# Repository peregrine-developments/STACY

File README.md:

# STACY
Requires symbols/footprints from [TheBoisCollective global library ](https://github.com/peregrine-developments/TBC_Global)

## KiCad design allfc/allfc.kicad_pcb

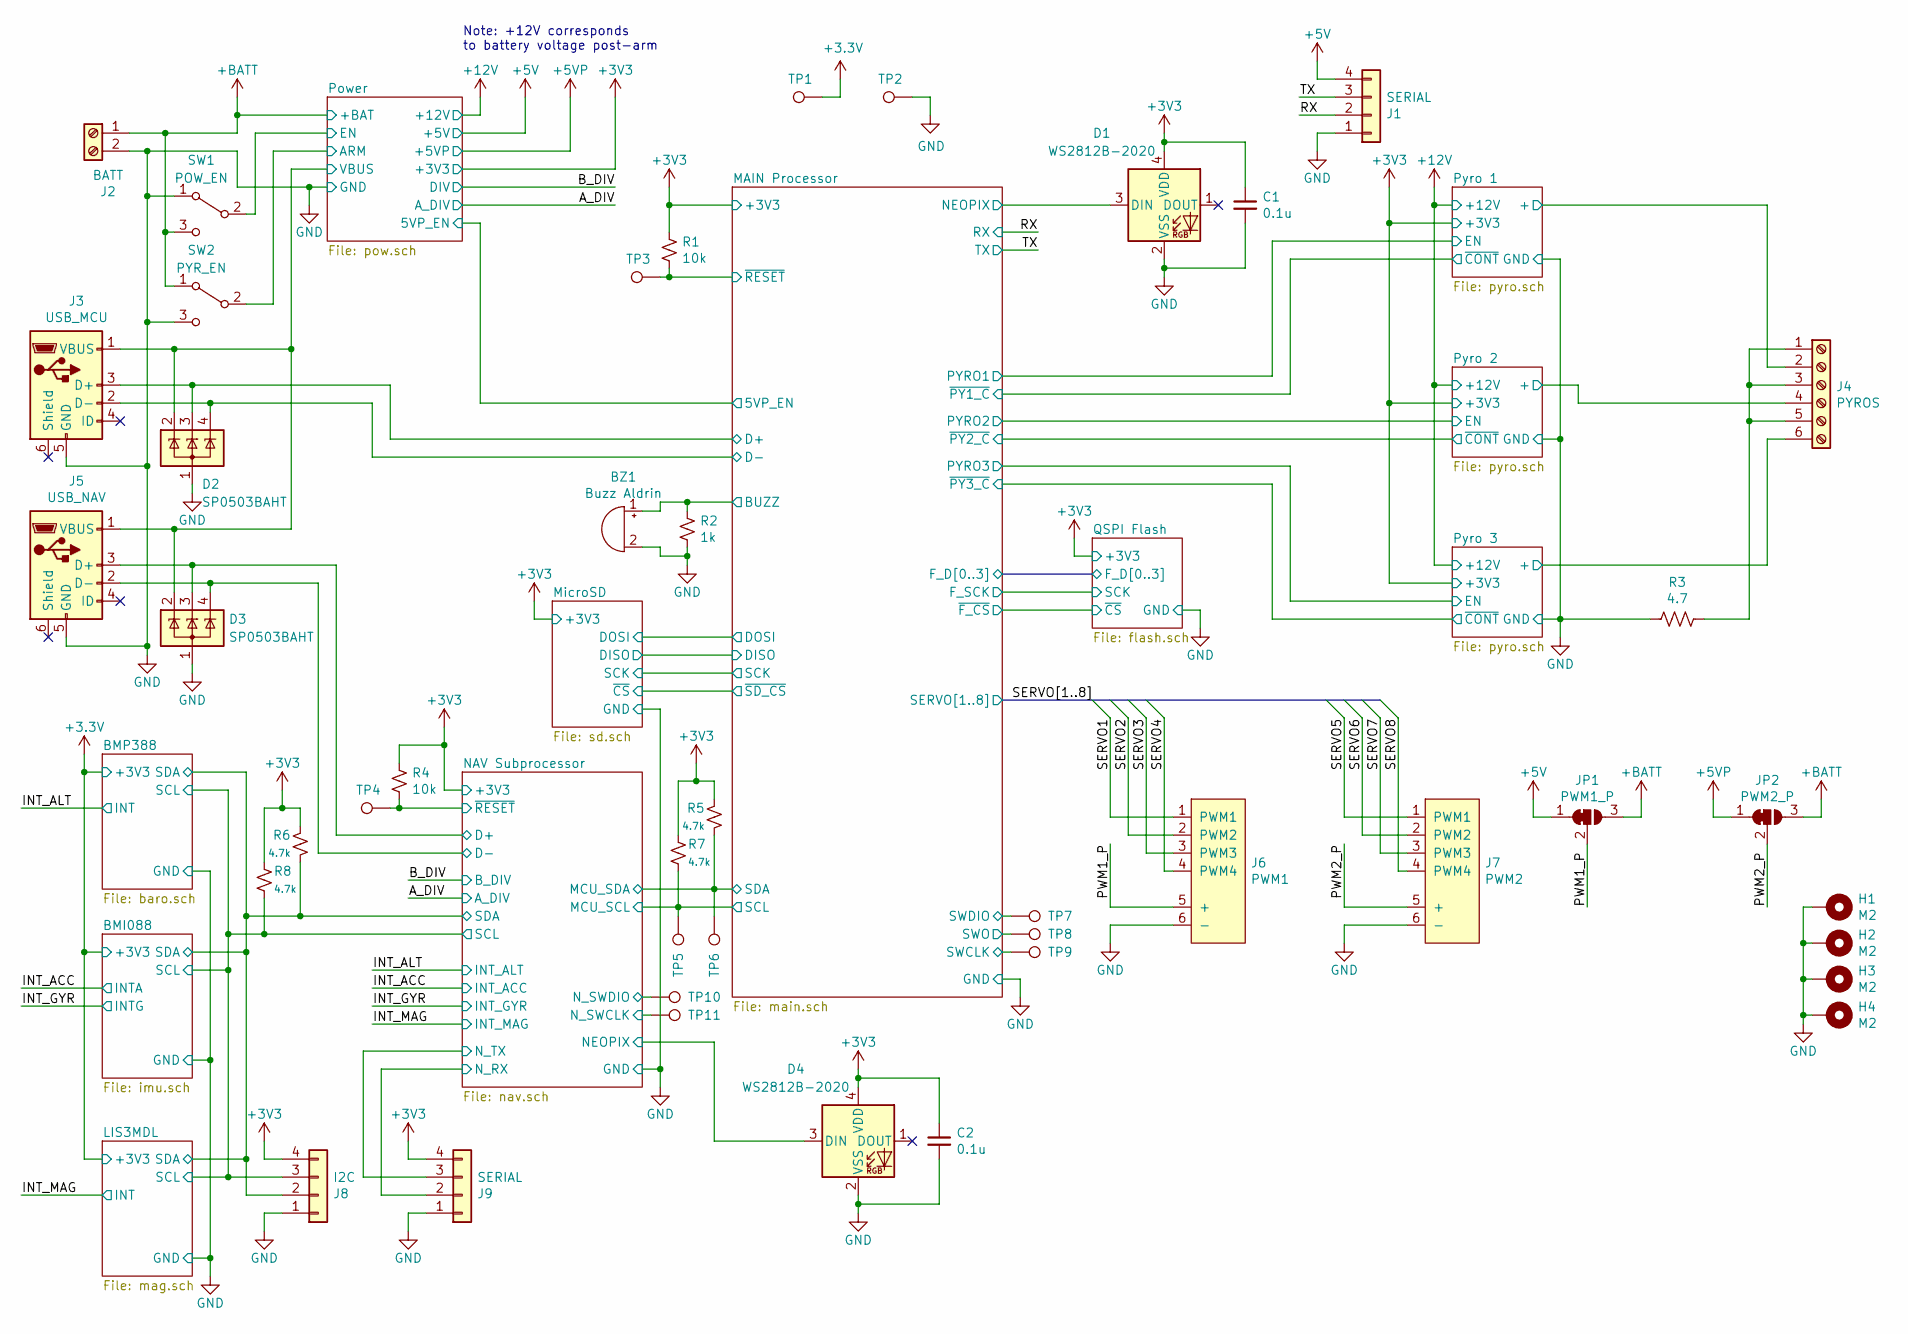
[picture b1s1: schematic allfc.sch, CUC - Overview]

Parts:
BZ1: Buzz Aldrin; Buzzer_CUI_CPT-9019S-SMT
C1, C2: 0.1u; C_0603_1608Metric
D1, D4: WS2812B-2020; WS2812B-2020_2x2mm
D2, D3: SP0503BAHT; SOT-143
H1, H2, H3, H4: M2; MountingHole_2.2mm_M2_Pad
J1, J9: SERIAL; JST_GH_BM04B-GHS-TBT_1x04-1MP_P1.25mm_Vertical
J2: BATT; TerminalBlock_Phoenix_MKDS-3-2-5.08_1x02_P5.08mm_Horizontal
J3: USB_MCU; USB_Micro-B_Molex_47346-0001_ShieldFloat
J4: PYROS; TerminalBlock_Phoenix_MKDS-3-6-5.08_1x06_P5.08mm_Horizontal
J5: USB_NAV; USB_Micro-B_Molex_47346-0001_ShieldFloat
J6: PWM1; PinHeader_3x04_P2.54mm_Vertical
J7: PWM2; PinHeader_3x04_P2.54mm_Vertical
J8: I2C; JST_GH_BM04B-GHS-TBT_1x04-1MP_P1.25mm_Vertical
JP1: PWM1_P; SolderJumper-3_P1.3mm_Bridged12_Pad1.0x1.5mm_NumberLabels
JP2: PWM2_P; SolderJumper-3_P1.3mm_Bridged12_Pad1.0x1.5mm_NumberLabels
R1, R4: 10k; R_0603_1608Metric
R2: 1k; R_0603_1608Metric
R3: 4.7; R_2512_6332Metric
R5, R6, R7, R8: 4.7k; R_0603_1608Metric
SW1: POW_EN; SW_SPDT_PCM12_HIDD
SW2: PYR_EN; SW_SPDT_PCM12_HIDD
TP1, TP2, TP3, TP4, TP5, TP6, TP7, TP8, TP9, TP10, TP11: TestPoint; TestPoint_THTPad_D1.0mm_Drill0.5mm

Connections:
+3V3: C1.1, C2.1, D1.4 (VDD), D4.4 (VDD), J8.4, J9.4, R1.2, R4.2, R5.1, R6.1, R7.1, R8.1, TP1.1; also elsewhere on the board
+5V: J1.4, JP1.1 (A); also elsewhere on the board
+5VP: JP2.1 (A); also elsewhere on the board
+BATT: J2.1, JP1.3 (B), JP2.3 (B), SW1.3 (C), SW2.1 (A); also elsewhere on the board
/BMI088/SCL: J8.3, R8.2; also elsewhere on the board
/BMI088/SDA: J8.2, R6.2; also elsewhere on the board
/MAIN Processor/BUZZ: BZ1.1 (-), R2.1; also elsewhere on the board
/MAIN Processor/D+: D2.3 (K), J3.3 (D+); also elsewhere on the board
/MAIN Processor/D-: D2.4 (K), J3.2 (D-); also elsewhere on the board
/MAIN Processor/NEOPIX: D1.3 (DIN); also elsewhere on the board
/MAIN Processor/SWCLK: TP9.1; also elsewhere on the board
/MAIN Processor/SWDIO: TP7.1; also elsewhere on the board
/MAIN Processor/SWO: TP8.1; also elsewhere on the board
/MAIN Processor/~RESET: R1.1, TP3.1; also elsewhere on the board
/NAV Subprocessor/D+: D3.3 (K), J5.3 (D+); also elsewhere on the board
/NAV Subprocessor/D-: D3.4 (K), J5.2 (D-); also elsewhere on the board
/NAV Subprocessor/MCU_SCL: R7.2, TP5.1; also elsewhere on the board
/NAV Subprocessor/MCU_SDA: R5.2, TP6.1; also elsewhere on the board
/NAV Subprocessor/NEOPIX: D4.3 (DIN); also elsewhere on the board
/NAV Subprocessor/N_RX: J9.2; also elsewhere on the board
/NAV Subprocessor/N_SWCLK: TP11.1; also elsewhere on the board
/NAV Subprocessor/N_SWDIO: TP10.1; also elsewhere on the board
/NAV Subprocessor/N_TX: J9.3; also elsewhere on the board
/NAV Subprocessor/~RESET: R4.1, TP4.1; also elsewhere on the board
/PWM1_P: J6.5 (+), JP1.2 (C)
/PWM2_P: J7.5 (+), JP2.2 (C)
/Power/ARM: SW2.2 (B); also elsewhere on the board
/Power/EN: SW1.2 (B); also elsewhere on the board
/Power/VBUS: D2.2 (K), D3.2 (K), J3.1 (VBUS), J5.1 (VBUS); also elsewhere on the board
/Pyro 1/+: J4.2; also elsewhere on the board
/Pyro 2/+: J4.4; also elsewhere on the board
/Pyro 3/+: J4.6; also elsewhere on the board
/RX: J1.2; also elsewhere on the board
/SERVO1: J6.1 (PWM1); also elsewhere on the board
/SERVO2: J6.2 (PWM2); also elsewhere on the board
/SERVO3: J6.3 (PWM3); also elsewhere on the board
/SERVO4: J6.4 (PWM4); also elsewhere on the board
/SERVO5: J7.1 (PWM1); also elsewhere on the board
/SERVO6: J7.2 (PWM2); also elsewhere on the board
/SERVO7: J7.3 (PWM3); also elsewhere on the board
/SERVO8: J7.4 (PWM4); also elsewhere on the board
/TX: J1.3; also elsewhere on the board
GND: BZ1.2 (+), C1.2, C2.2, D1.2 (VSS), D2.1 (A), D3.1 (A), D4.2 (VSS), H1.1, H2.1, H3.1, H4.1, J1.1, J2.2, J3.5 (GND), J5.5 (GND), J6.6 (-), J7.6 (-), J8.1, J9.1, R2.2, R3.2, SW1.1 (A), SW2.3 (C), TP2.1; also elsewhere on the board
unnamed: J4.1, J4.3, J4.5, R3.1

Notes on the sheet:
Note: +12V corresponds to battery voltage post-arm

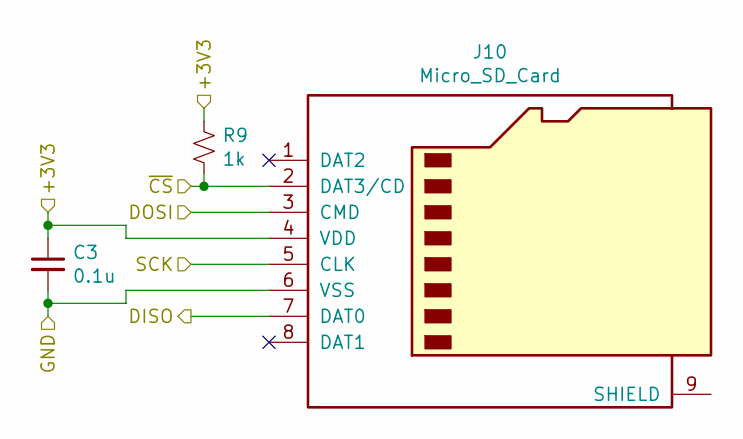
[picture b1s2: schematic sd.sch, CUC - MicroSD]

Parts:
C3: 0.1u; C_0603_1608Metric
J10: Micro_SD_Card; microSD_HC_Hirose_DM3D-SF
R9: 1k; R_0603_1608Metric

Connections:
+3V3: C3.1, J10.4 (VDD), R9.1; also elsewhere on the board
/MAIN Processor/DISO: J10.7 (DAT0); also elsewhere on the board
/MAIN Processor/DOSI: J10.3 (CMD); also elsewhere on the board
/MAIN Processor/SCK: J10.5 (CLK); also elsewhere on the board
/MicroSD/~CS: J10.2 (DAT3/CD), R9.2; also elsewhere on the board
GND: C3.2, J10.6 (VSS); also elsewhere on the board

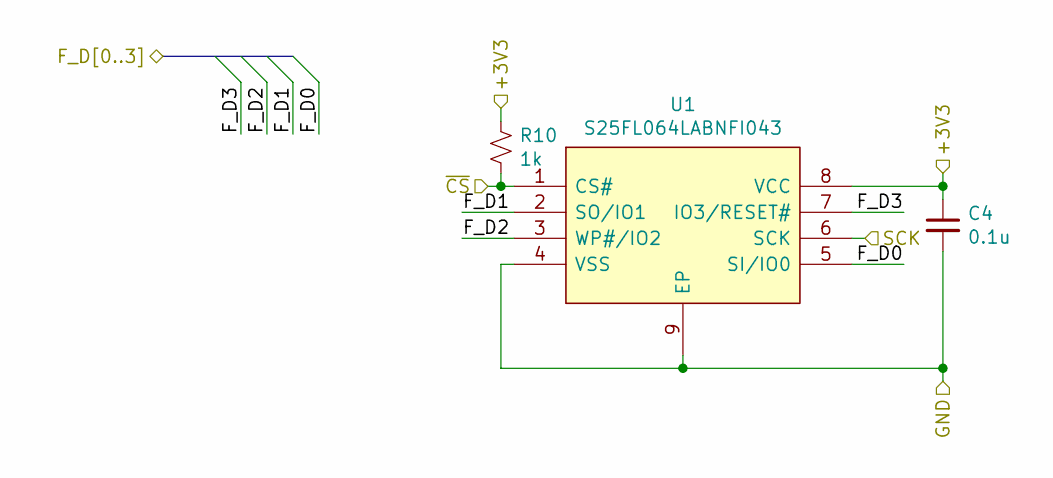
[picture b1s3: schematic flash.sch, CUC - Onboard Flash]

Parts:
C4: 0.1u; C_0603_1608Metric
R10: 1k; R_0603_1608Metric
U1: S25FL064LABNFI043; SON80P400X400X60-9N; Mouser Part Number 727-S25FL064LABNF043

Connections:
+3V3: C4.1, R10.1, U1.8 (VCC); also elsewhere on the board
/MAIN Processor/F_D0: U1.5 (SI/IO0); also elsewhere on the board
/MAIN Processor/F_D1: U1.2 (SO/IO1); also elsewhere on the board
/MAIN Processor/F_D2: U1.3 (WP#/IO2); also elsewhere on the board
/MAIN Processor/F_D3: U1.7 (IO3/RESET#); also elsewhere on the board
/MAIN Processor/F_SCK: U1.6 (SCK); also elsewhere on the board
/QSPI Flash/~CS: R10.2, U1.1 (CS#); also elsewhere on the board
GND: C4.2, U1.4 (VSS), U1.9 (EP); also elsewhere on the board

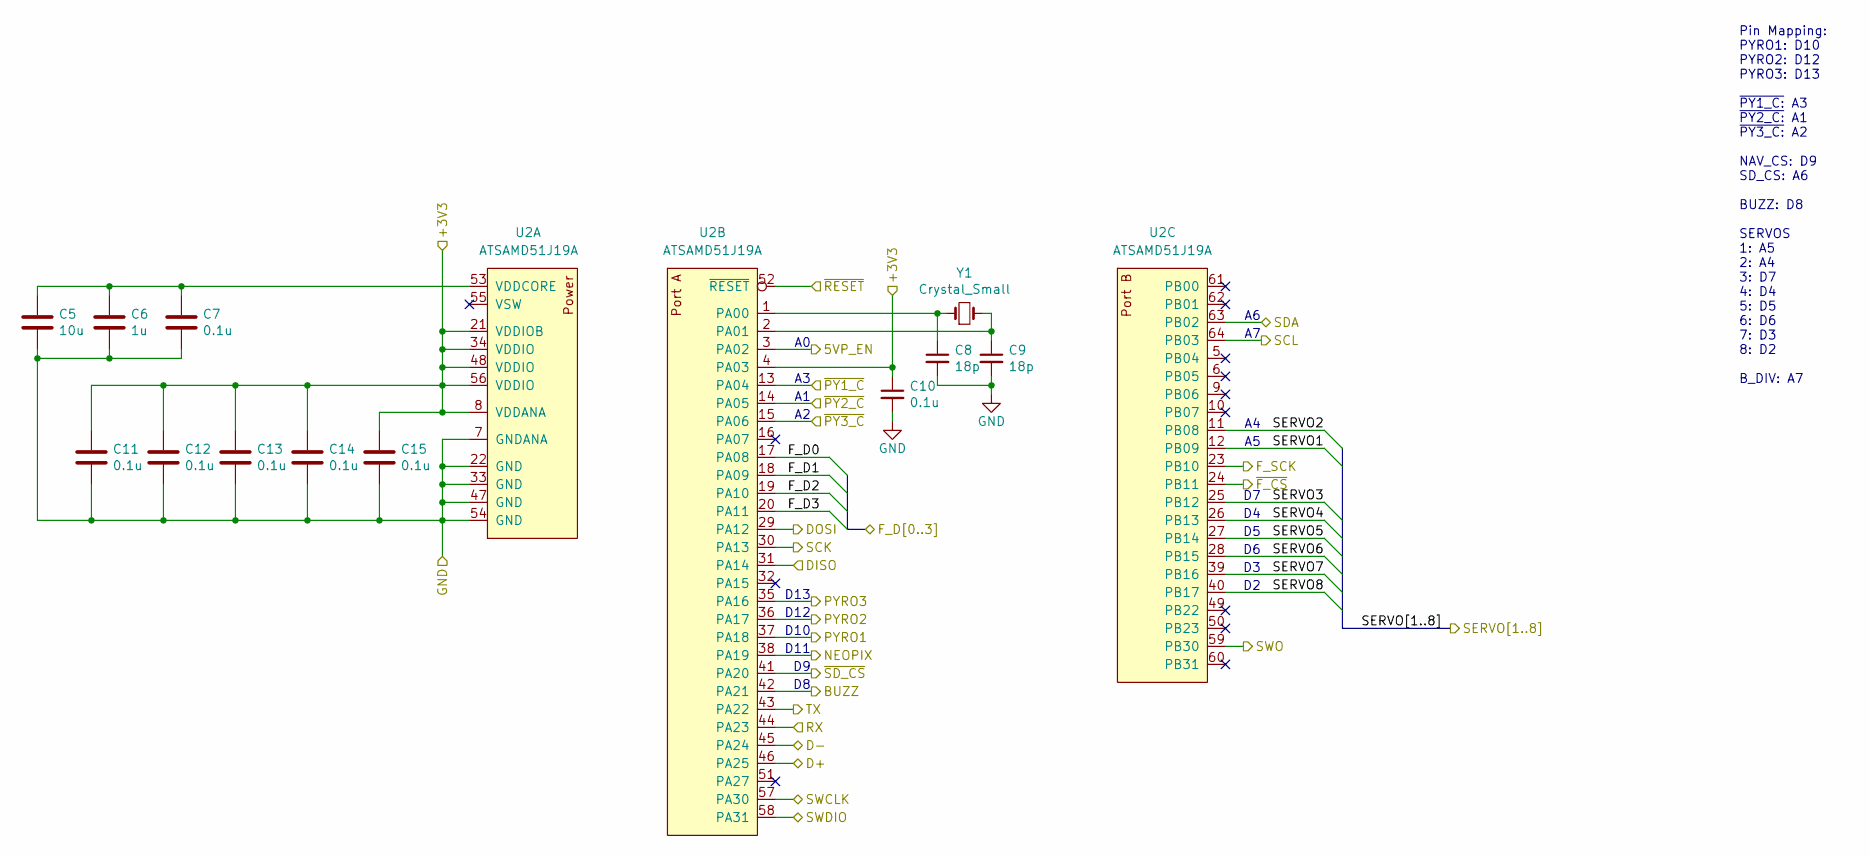
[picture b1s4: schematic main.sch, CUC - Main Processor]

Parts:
C5: 10u; C_0603_1608Metric
C6: 1u; C_0603_1608Metric
C7, C10, C11, C12, C13, C14, C15: 0.1u; C_0603_1608Metric
C8, C9: 18p; C_0402_1005Metric
U2: ATSAMD51J19A; QFN-64-1EP_9x9mm_P0.5mm_EP4.7x4.7mm
Y1: Crystal_Small; Crystal_SMD_2012-2Pin_2.0x1.2mm

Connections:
+3V3: C10.1, C11.1, C12.1, C13.1, C14.1, C15.1, U2.4 (PA03), U2.8 (VDDANA), U2.21 (VDDIOB), U2.34 (VDDIO), U2.48 (VDDIO), U2.56 (VDDIO); also elsewhere on the board
/MAIN Processor/5VP_EN: U2.3 (PA02); also elsewhere on the board
/MAIN Processor/BUZZ: U2.42 (PA21); also elsewhere on the board
/MAIN Processor/D+: U2.46 (PA25); also elsewhere on the board
/MAIN Processor/D-: U2.45 (PA24); also elsewhere on the board
/MAIN Processor/DISO: U2.31 (PA14); also elsewhere on the board
/MAIN Processor/DOSI: U2.29 (PA12); also elsewhere on the board
/MAIN Processor/F_D0: U2.17 (PA08); also elsewhere on the board
/MAIN Processor/F_D1: U2.18 (PA09); also elsewhere on the board
/MAIN Processor/F_D2: U2.19 (PA10); also elsewhere on the board
/MAIN Processor/F_D3: U2.20 (PA11); also elsewhere on the board
/MAIN Processor/F_SCK: U2.23 (PB10); also elsewhere on the board
/MAIN Processor/NEOPIX: U2.38 (PA19); also elsewhere on the board
/MAIN Processor/SCK: U2.30 (PA13); also elsewhere on the board
/MAIN Processor/SWCLK: U2.57 (PA30); also elsewhere on the board
/MAIN Processor/SWDIO: U2.58 (PA31); also elsewhere on the board
/MAIN Processor/SWO: U2.59 (PB30); also elsewhere on the board
/MAIN Processor/~RESET: U2.52 (~RESET); also elsewhere on the board
/MicroSD/~CS: U2.41 (PA20); also elsewhere on the board
/NAV Subprocessor/MCU_SCL: U2.64 (PB03); also elsewhere on the board
/NAV Subprocessor/MCU_SDA: U2.63 (PB02); also elsewhere on the board
/Pyro 1/EN: U2.37 (PA18); also elsewhere on the board
/Pyro 1/~CONT: U2.13 (PA04); also elsewhere on the board
/Pyro 2/EN: U2.36 (PA17); also elsewhere on the board
/Pyro 2/~CONT: U2.14 (PA05); also elsewhere on the board
/Pyro 3/EN: U2.35 (PA16); also elsewhere on the board
/Pyro 3/~CONT: U2.15 (PA06); also elsewhere on the board
/QSPI Flash/~CS: U2.24 (PB11); also elsewhere on the board
/RX: U2.44 (PA23); also elsewhere on the board
/SERVO1: U2.12 (PB09); also elsewhere on the board
/SERVO2: U2.11 (PB08); also elsewhere on the board
/SERVO3: U2.25 (PB12); also elsewhere on the board
/SERVO4: U2.26 (PB13); also elsewhere on the board
/SERVO5: U2.27 (PB14); also elsewhere on the board
/SERVO6: U2.28 (PB15); also elsewhere on the board
/SERVO7: U2.39 (PB16); also elsewhere on the board
/SERVO8: U2.40 (PB17); also elsewhere on the board
/TX: U2.43 (PA22); also elsewhere on the board
GND: C5.2, C6.2, C7.2, C8.2, C9.2, C10.2, C11.2, C12.2, C13.2, C14.2, C15.2, U2.7 (GNDANA), U2.22 (GND), U2.33 (GND), U2.47 (GND), U2.54 (GND); also elsewhere on the board
unnamed: C5.1, C6.1, C7.1, U2.53 (VDDCORE)
unnamed: C8.1, U2.1 (PA00), Y1.1
unnamed: C9.1, U2.2 (PA01), Y1.2

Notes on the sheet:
Pin Mapping: PYRO1: D10 PYRO2: D12 PYRO3: D13 ~PY1_C:~ A3 ~PY2_C:~ A1 ~PY3_C:~ A2 NAV_CS: D9 SD_CS: A6 BUZZ: D8 SERVOS 1: A5 2: A4 3: D7 4: D4 5: D5 6: D6 7: D3 8: D2 B_DIV: A7
D11
D10
D12
D13

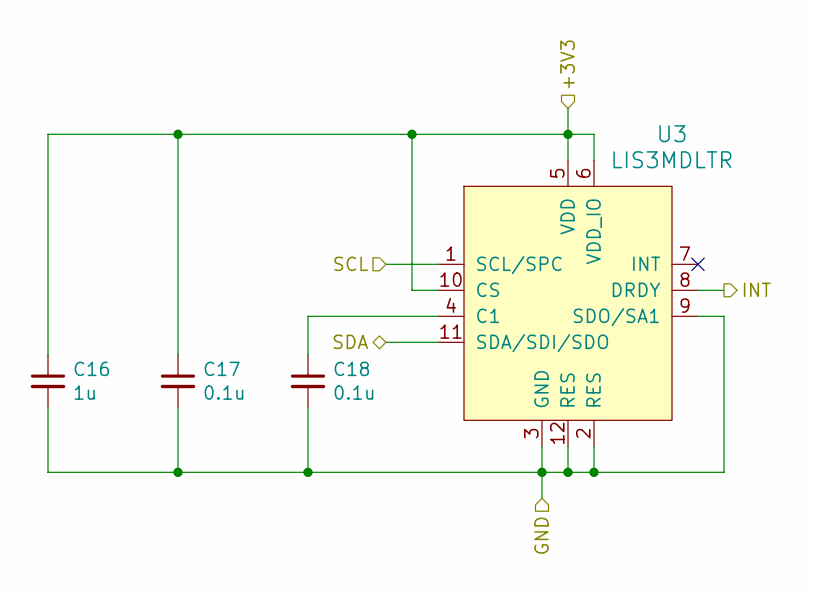
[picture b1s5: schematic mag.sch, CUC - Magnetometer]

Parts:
C16: 1u; C_0603_1608Metric
C17, C18: 0.1u; C_0603_1608Metric
U3: LIS3MDLTR; VFLGA-12_2x2mm; MPN LIS3MDLTR; Digi-Key_PN 497-13892-1-ND

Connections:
+3V3: C16.1, C17.1, U3.5 (VDD), U3.6 (VDD_IO), U3.10 (CS); also elsewhere on the board
/BMI088/SCL: U3.1 (SCL/SPC); also elsewhere on the board
/BMI088/SDA: U3.11 (SDA/SDI/SDO); also elsewhere on the board
/INT_MAG: U3.8 (DRDY); also elsewhere on the board
GND: C16.2, C17.2, C18.2, U3.2 (RES), U3.3 (GND), U3.9 (SDO/SA1), U3.12 (RES); also elsewhere on the board
unnamed: C18.1, U3.4 (C1)

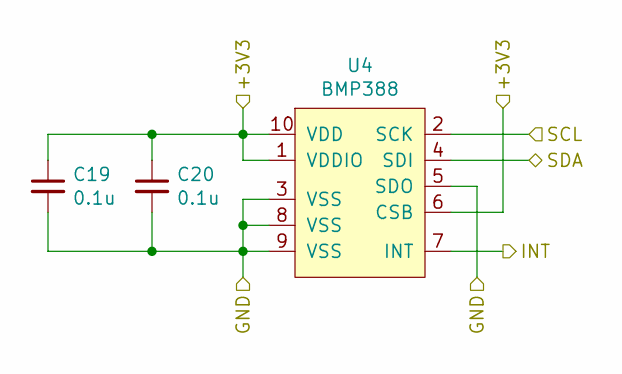
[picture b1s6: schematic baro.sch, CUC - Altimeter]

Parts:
C19, C20: 0.1u; C_0603_1608Metric
U4: BMP388

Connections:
+3V3: C19.1, C20.1, U4.1 (VDDIO), U4.6 (CSB), U4.10 (VDD); also elsewhere on the board
/BMI088/SCL: U4.2 (SCK); also elsewhere on the board
/BMI088/SDA: U4.4 (SDI); also elsewhere on the board
/INT_ALT: U4.7 (INT); also elsewhere on the board
GND: C19.2, C20.2, U4.3 (VSS), U4.5 (SDO), U4.8 (VSS), U4.9 (VSS); also elsewhere on the board

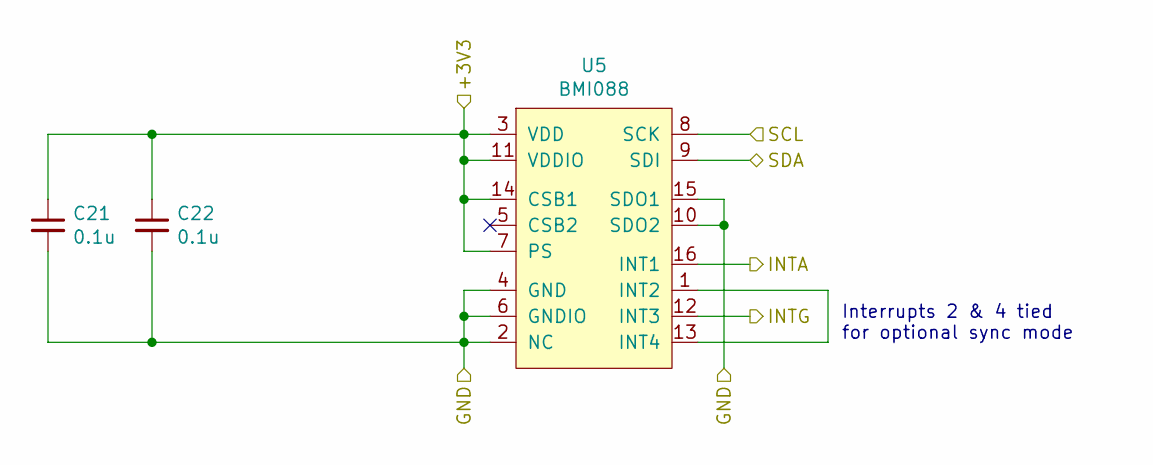
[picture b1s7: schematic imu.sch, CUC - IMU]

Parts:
C21, C22: 0.1u; C_0603_1608Metric
U5: BMI088; VQFN16_4.5x3.0mm

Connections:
+3V3: C21.1, C22.1, U5.3 (VDD), U5.7 (PS), U5.11 (VDDIO), U5.14 (CSB1); also elsewhere on the board
/BMI088/SCL: U5.8 (SCK); also elsewhere on the board
/BMI088/SDA: U5.9 (SDI); also elsewhere on the board
/INT_ACC: U5.16 (INT1); also elsewhere on the board
/INT_GYR: U5.12 (INT3); also elsewhere on the board
GND: C21.2, C22.2, U5.2 (NC), U5.4 (GND), U5.6 (GNDIO), U5.10 (SDO2), U5.15 (SDO1); also elsewhere on the board
unnamed: U5.1 (INT2), U5.13 (INT4)

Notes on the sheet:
Interrupts 2 & 4 tied for optional sync mode

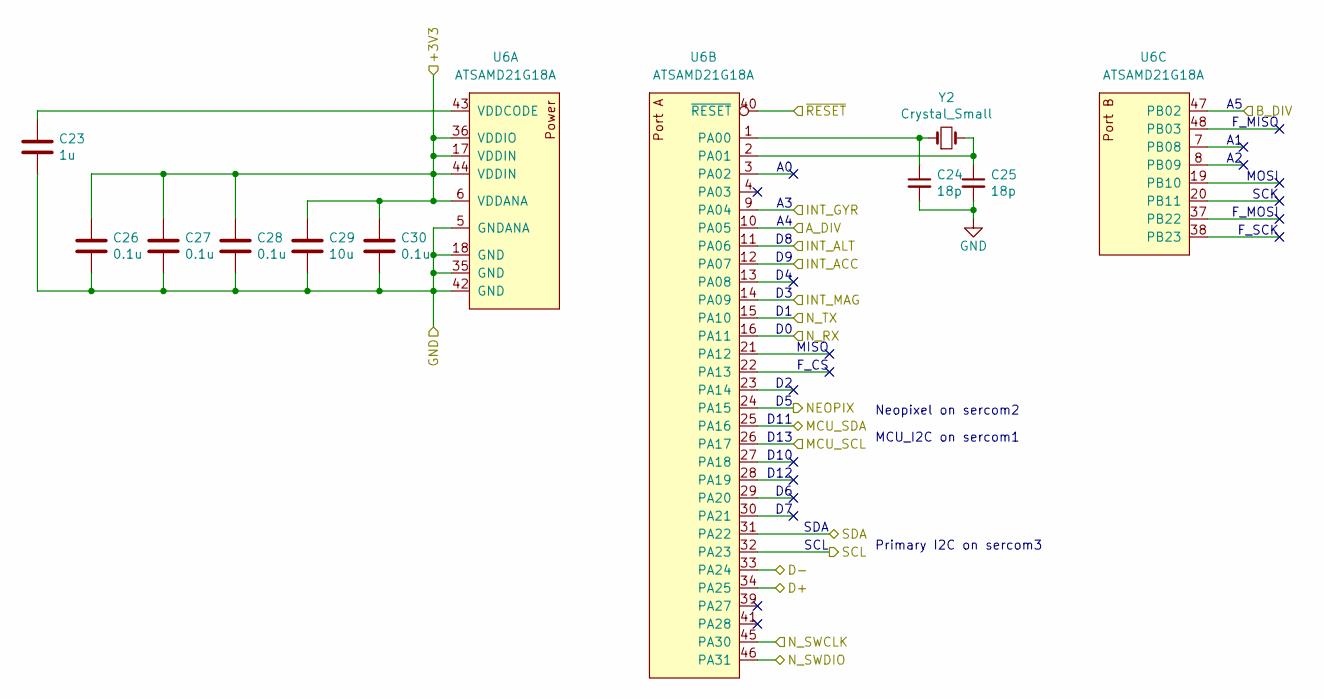
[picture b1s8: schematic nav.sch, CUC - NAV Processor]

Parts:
C23: 1u; C_0603_1608Metric
C24, C25: 18p; C_0402_1005Metric
C26, C27, C28, C30: 0.1u; C_0603_1608Metric
C29: 10u; C_0603_1608Metric
U6: ATSAMD21G18A; VQFN-48-1EP_7x7mm_P0.5mm_EP5.15x5.15mm
Y2: Crystal_Small; Crystal_SMD_2012-2Pin_2.0x1.2mm

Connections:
+3V3: C26.1, C27.1, C28.1, C29.1, C30.1, U6.6 (VDDANA), U6.17 (VDDIN), U6.36 (VDDIO), U6.44 (VDDIN); also elsewhere on the board
/A_DIV: U6.10 (PA05); also elsewhere on the board
/BMI088/SCL: U6.32 (PA23); also elsewhere on the board
/BMI088/SDA: U6.31 (PA22); also elsewhere on the board
/B_DIV: U6.47 (PB02); also elsewhere on the board
/INT_ACC: U6.12 (PA07); also elsewhere on the board
/INT_ALT: U6.11 (PA06); also elsewhere on the board
/INT_GYR: U6.9 (PA04); also elsewhere on the board
/INT_MAG: U6.14 (PA09); also elsewhere on the board
/NAV Subprocessor/D+: U6.34 (PA25); also elsewhere on the board
/NAV Subprocessor/D-: U6.33 (PA24); also elsewhere on the board
/NAV Subprocessor/MCU_SCL: U6.26 (PA17); also elsewhere on the board
/NAV Subprocessor/MCU_SDA: U6.25 (PA16); also elsewhere on the board
/NAV Subprocessor/NEOPIX: U6.24 (PA15); also elsewhere on the board
/NAV Subprocessor/N_RX: U6.16 (PA11); also elsewhere on the board
/NAV Subprocessor/N_SWCLK: U6.45 (PA30); also elsewhere on the board
/NAV Subprocessor/N_SWDIO: U6.46 (PA31); also elsewhere on the board
/NAV Subprocessor/N_TX: U6.15 (PA10); also elsewhere on the board
/NAV Subprocessor/~RESET: U6.40 (~RESET); also elsewhere on the board
GND: C23.2, C24.2, C25.2, C26.2, C27.2, C28.2, C29.2, C30.2, U6.5 (GNDANA), U6.18 (GND), U6.35 (GND), U6.42 (GND); also elsewhere on the board
unnamed: C23.1, U6.43 (VDDCODE)
unnamed: C24.1, U6.1 (PA00), Y2.1
unnamed: C25.1, U6.2 (PA01), Y2.2

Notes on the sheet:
Primary I2C on sercom3
MISO
F_CS
D11
D13
D10
SDA
SCL
F_MISO
MOSI
SCK
F_MOSI
F_SCK
D12
MCU_I2C on sercom1
Neopixel on sercom2

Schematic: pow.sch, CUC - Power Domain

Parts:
C31, C34, C37: 0.1u; C_0603_1608Metric
C32, C38: 47p; C_0603_1608Metric
C33, C35, C39: 10u; C_0603_1608Metric
C36, C40: 47u; C_0805_2012Metric
C41, C42: 1u; C_0603_1608Metric
D5: D_Schottky_Small; D_SOD-323
D6, D7, D8: RED; LED_0603_1608Metric
D9: ORANGE; LED_0603_1608Metric
L1, L2: 6.8u; L_Bourns_SRP7028A_7.3x6.6mm
Q1: CXDM4060P; SOT-89-3
Q2: DMP3098L-7; SOT-23
R11, R12, R16, R23: 4.7k; R_0603_1608Metric
R13, R14: 470; R_0603_1608Metric
R15, R18: 158k; R_0603_1608Metric
R17, R24, R25, R26: 30.1k; R_0603_1608Metric
R19, R20: 86.6k; R_0603_1608Metric
R21, R22: 1k; R_0603_1608Metric
R27: 82; R_0603_1608Metric
R28, R29: 180; R_0603_1608Metric
R30: 820; R_0603_1608Metric
U7: ‎MIC5216-3.3; SOT-23-5
U8, U9: AP63300WU-7; SOT95P280X90-6N; Mouser Part Number 621-AP63300WU-7

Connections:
+3V3: C34.1, D6.2 (A), U7.5 (OUT); also elsewhere on the board
+5V: C32.1, C36.1, D5.2 (A), D7.2 (A), L1.2, R12.1, R14.1, R15.1; also elsewhere on the board
+5VP: C38.1, C40.1, D8.2 (A), L2.2, R18.1; also elsewhere on the board
+12V: D9.2 (A), Q1.2 (D), R20.1; also elsewhere on the board
+BATT: C35.2, C39.2, Q1.3 (S), R11.2, R19.1, U8.3 (VIN), U9.3 (VIN); also elsewhere on the board
/A_DIV: C42.1, R22.1; also elsewhere on the board
/B_DIV: C41.1, R21.1; also elsewhere on the board
/MAIN Processor/5VP_EN: R23.1, U9.2 (EN); also elsewhere on the board
/Power/5VP_FB: C38.2, R18.2, R24.1, U9.1 (FB)
/Power/5V_FB: C32.2, R15.2, R17.1, U8.1 (FB)
/Power/+5Vi: C33.1, D5.1 (K), Q2.3 (D), U7.1 (IN), U7.3 (EN)
/Power/ARM: R11.1, R13.1; also elsewhere on the board
/Power/EN: R16.1, U8.2 (EN); also elsewhere on the board
/Power/VBUS: Q2.2 (S); also elsewhere on the board
GND: C33.2, C34.2, C35.1, C36.2, C39.1, C40.2, C41.2, C42.2, R12.2, R16.2, R17.2, R23.2, R24.2, R25.2, R26.2, R27.2, R28.2, R29.2, R30.2, U7.2 (GND), U8.4 (GND), U9.4 (GND); also elsewhere on the board
unnamed: C31.1, L1.1, U8.5 (SW)
unnamed: C31.2, U8.6 (BST)
unnamed: C37.1, L2.1, U9.5 (SW)
unnamed: C37.2, U9.6 (BST)
unnamed: D6.1 (K), R27.1
unnamed: D7.1 (K), R28.1
unnamed: D8.1 (K), R29.1
unnamed: D9.1 (K), R30.1
unnamed: Q1.1 (G), R13.2
unnamed: Q2.1 (G), R14.2
unnamed: R19.2, R21.2, R25.1
unnamed: R20.2, R22.2, R26.1

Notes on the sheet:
5V Regulator
5VP Regulator
12V Pyro Arm
3.3V Regulator
Battery Divider
5Vi Switch
Indicators
+12V Divider
+12V divider is necessary due to the behavior of the pyro continuity network. When no voltage is measured at the continuity point, either there is a valid charge present OR the line is not armed.

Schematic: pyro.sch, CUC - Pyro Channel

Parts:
C43, C44: 10u; C_0603_1608Metric
R31: 10k; R_0603_1608Metric
R32: 86.6k; R_0603_1608Metric
R33: 47; R_0603_1608Metric
R34: 1k; R_0603_1608Metric
R35: 470; R_0603_1608Metric
R36: 30.1k; R_0603_1608Metric
U10: UCS3205; VQFN19_3.0x3.0mm_2EP

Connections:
+3V3: U10.12 (LATCH); also elsewhere on the board
+12V: C43.1, R31.2, U10.19 (VIN), U10.20 (VOUT), U10.22 (VIN); also elsewhere on the board
/Pyro 1/+: C44.1, R31.1, R32.1, U10.16 (VOUT), U10.17 (VOUT), U10.21 (VOUT); also elsewhere on the board
/Pyro 1/EN: R33.2, R35.1; also elsewhere on the board
/Pyro 1/~CONT: R32.2, R36.1; also elsewhere on the board
GND: C43.2, C44.2, R34.2, R35.2, R36.2, U10.1 (GND), U10.3 (FRS), U10.4 (DIR), U10.5 (DSC), U10.14 (VOV), U10.15 (GND); also elsewhere on the board
unnamed: R33.1, U10.2 (EN)
unnamed: R34.1, U10.13 (ISEN)

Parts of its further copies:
C45, C46, C47, C48: 10u; C_0603_1608Metric
R37, R43: 10k; R_0603_1608Metric
R38, R44: 86.6k; R_0603_1608Metric
R39, R45: 47; R_0603_1608Metric
R40, R46: 1k; R_0603_1608Metric
R41, R47: 470; R_0603_1608Metric
R42, R48: 30.1k; R_0603_1608Metric
U11, U12: UCS3205; VQFN19_3.0x3.0mm_2EP

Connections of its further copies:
+3V3: U11.12 (LATCH), U12.12 (LATCH); also elsewhere on the board
+12V: C45.1, C47.1, R37.2, R43.2, U11.19 (VIN), U11.20 (VOUT), U11.22 (VIN), U12.19 (VIN), U12.20 (VOUT), U12.22 (VIN); also elsewhere on the board
/Pyro 2/+: C46.1, R37.1, R38.1, U11.16 (VOUT), U11.17 (VOUT), U11.21 (VOUT); also elsewhere on the board
/Pyro 2/EN: R39.2, R41.1; also elsewhere on the board
/Pyro 2/~CONT: R38.2, R42.1; also elsewhere on the board
/Pyro 3/+: C48.1, R43.1, R44.1, U12.16 (VOUT), U12.17 (VOUT), U12.21 (VOUT); also elsewhere on the board
/Pyro 3/EN: R45.2, R47.1; also elsewhere on the board
/Pyro 3/~CONT: R44.2, R48.1; also elsewhere on the board
GND: C45.2, C46.2, C47.2, C48.2, R40.2, R41.2, R42.2, R46.2, R47.2, R48.2, U11.1 (GND), U11.3 (FRS), U11.4 (DIR), U11.5 (DSC), U11.14 (VOV), U11.15 (GND), U12.1 (GND), U12.3 (FRS), U12.4 (DIR), U12.5 (DSC), U12.14 (VOV), U12.15 (GND); also elsewhere on the board
unnamed: R39.1, U11.2 (EN)
unnamed: R40.1, U11.13 (ISEN)
unnamed: R45.1, U12.2 (EN)
unnamed: R46.1, U12.13 (ISEN)

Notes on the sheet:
Trickle resistor allows small continuity current bypass
Charge present bypasses continuity divider

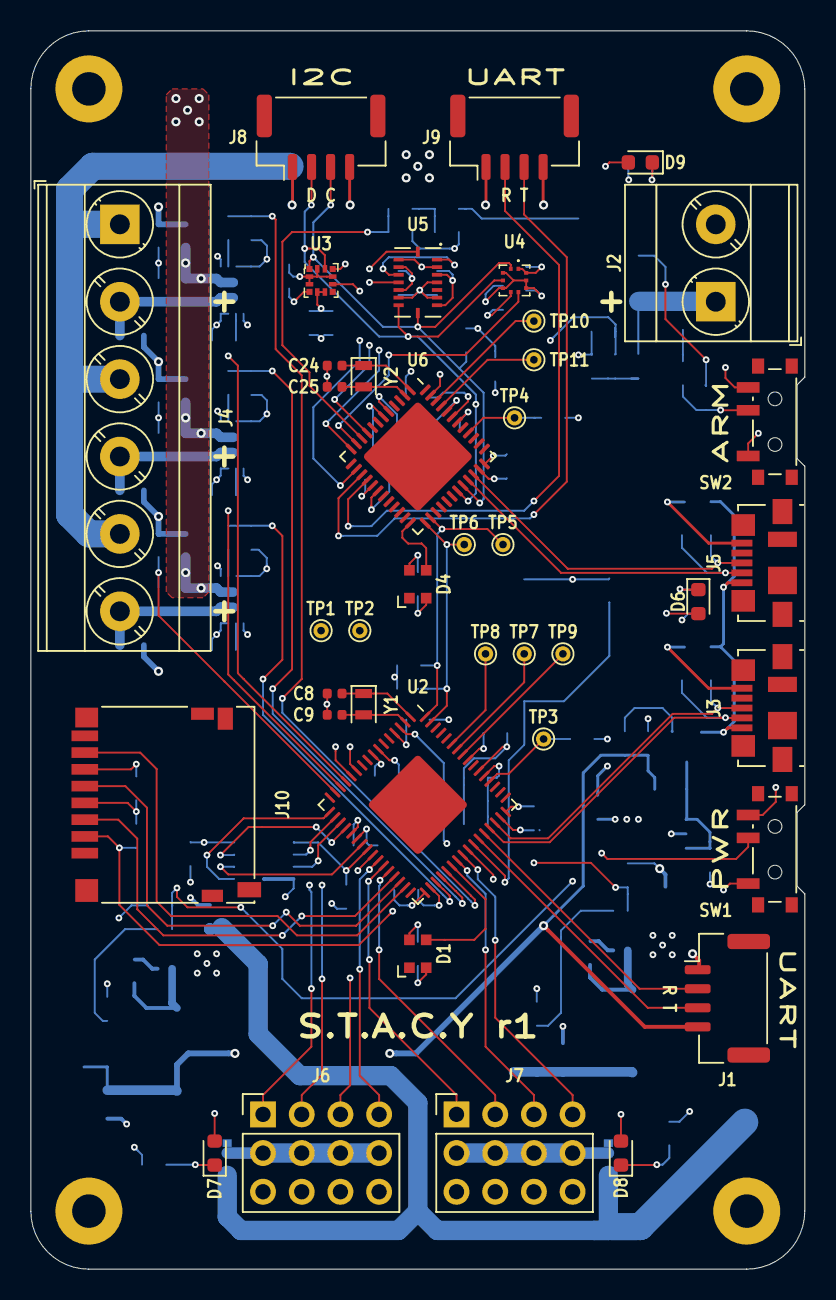
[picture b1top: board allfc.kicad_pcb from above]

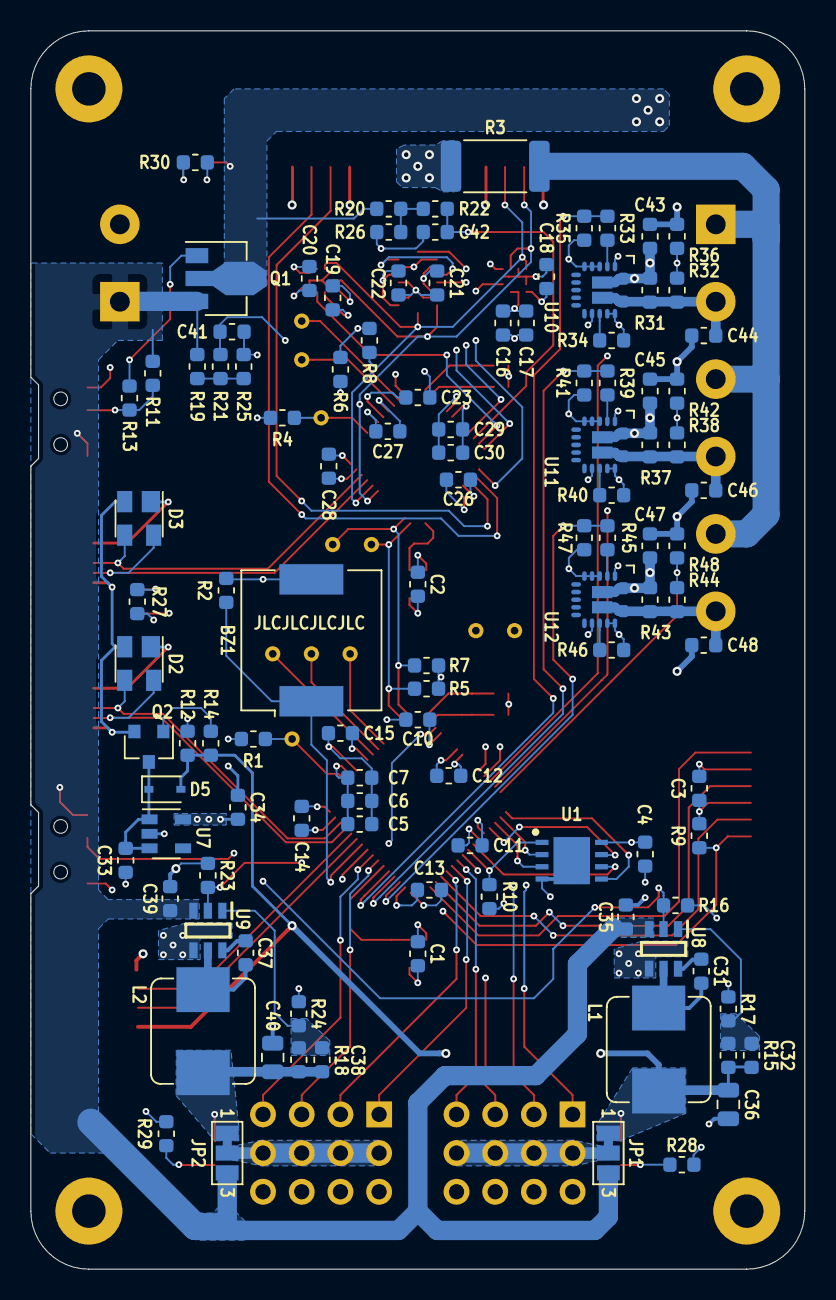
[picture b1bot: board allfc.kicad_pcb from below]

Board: 4 copper layers, 50.8 x 81.3 mm, 153 parts (109 on the bottom side), 97 nets.

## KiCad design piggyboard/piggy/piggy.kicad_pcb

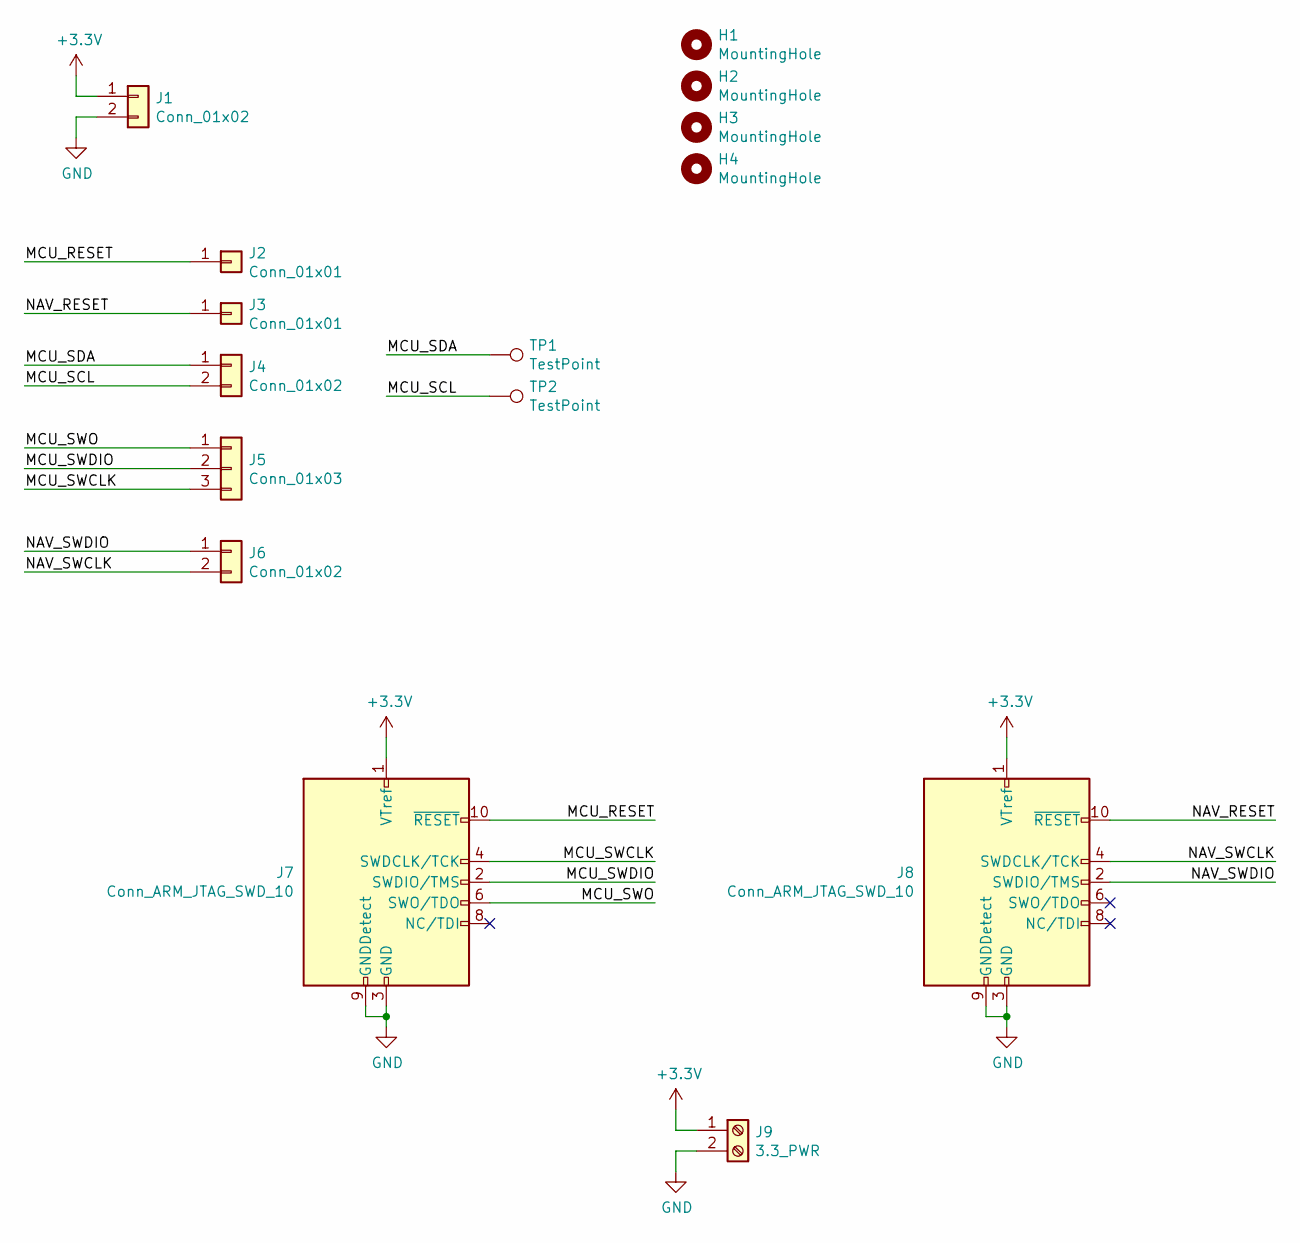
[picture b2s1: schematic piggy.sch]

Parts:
H1, H2, H3, H4: MountingHole; MountingHole_2.2mm_M2_Pad
J1, J4, J6: Conn_01x02; PinHeader_1x02_P2.54mm_Vertical
J2, J3: Conn_01x01; PinHeader_1x01_P2.54mm_Vertical
J5: Conn_01x03; PinHeader_1x03_P2.54mm_Vertical
J7, J8: Conn_ARM_JTAG_SWD_10; PinHeader_2x05_P1.27mm_Vertical_SMD
J9: 3.3_PWR; TerminalBlock_Phoenix_MKDS-3-2-5.08_1x02_P5.08mm_Horizontal
TP1, TP2: TestPoint; TestPoint_Bridge_Pitch2.54mm_Drill1.0mm

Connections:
+3V3: J1.1, J7.1 (VTref), J8.1 (VTref), J9.1
/MCU_RESET: J2.1, J7.10 (~RESET~)
/MCU_SCL: J4.2, TP2.1
/MCU_SDA: J4.1, TP1.1
/MCU_SWCLK: J5.3, J7.4 (SWDCLK/TCK)
/MCU_SWDIO: J5.2, J7.2 (SWDIO/TMS)
/MCU_SWO: J5.1, J7.6 (SWO/TDO)
/NAV_RESET: J3.1, J8.10 (~RESET~)
/NAV_SWCLK: J6.2, J8.4 (SWDCLK/TCK)
/NAV_SWDIO: J6.1, J8.2 (SWDIO/TMS)
GND: J1.2, J7.3 (GND), J7.5 (GND), J7.9 (GNDDetect), J8.3 (GND), J8.5 (GND), J8.9 (GNDDetect), J9.2

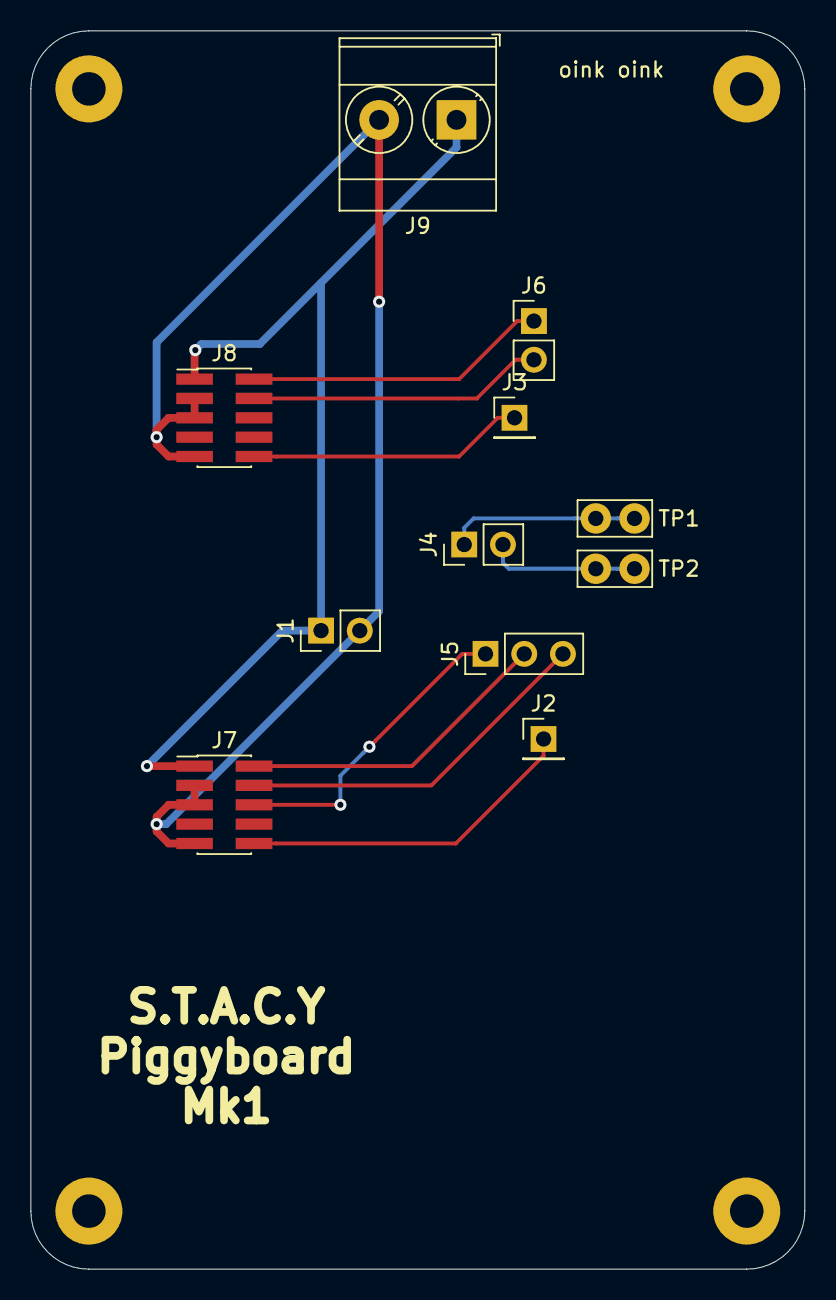
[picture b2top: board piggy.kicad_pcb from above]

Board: 2 copper layers, 50.8 x 81.3 mm, 15 parts (0 on the bottom side), 11 nets.

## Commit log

2021-08-03 initial upload
2021-08-03 release 1 schematic pdf
2022-02-06 Mount 3D Files
